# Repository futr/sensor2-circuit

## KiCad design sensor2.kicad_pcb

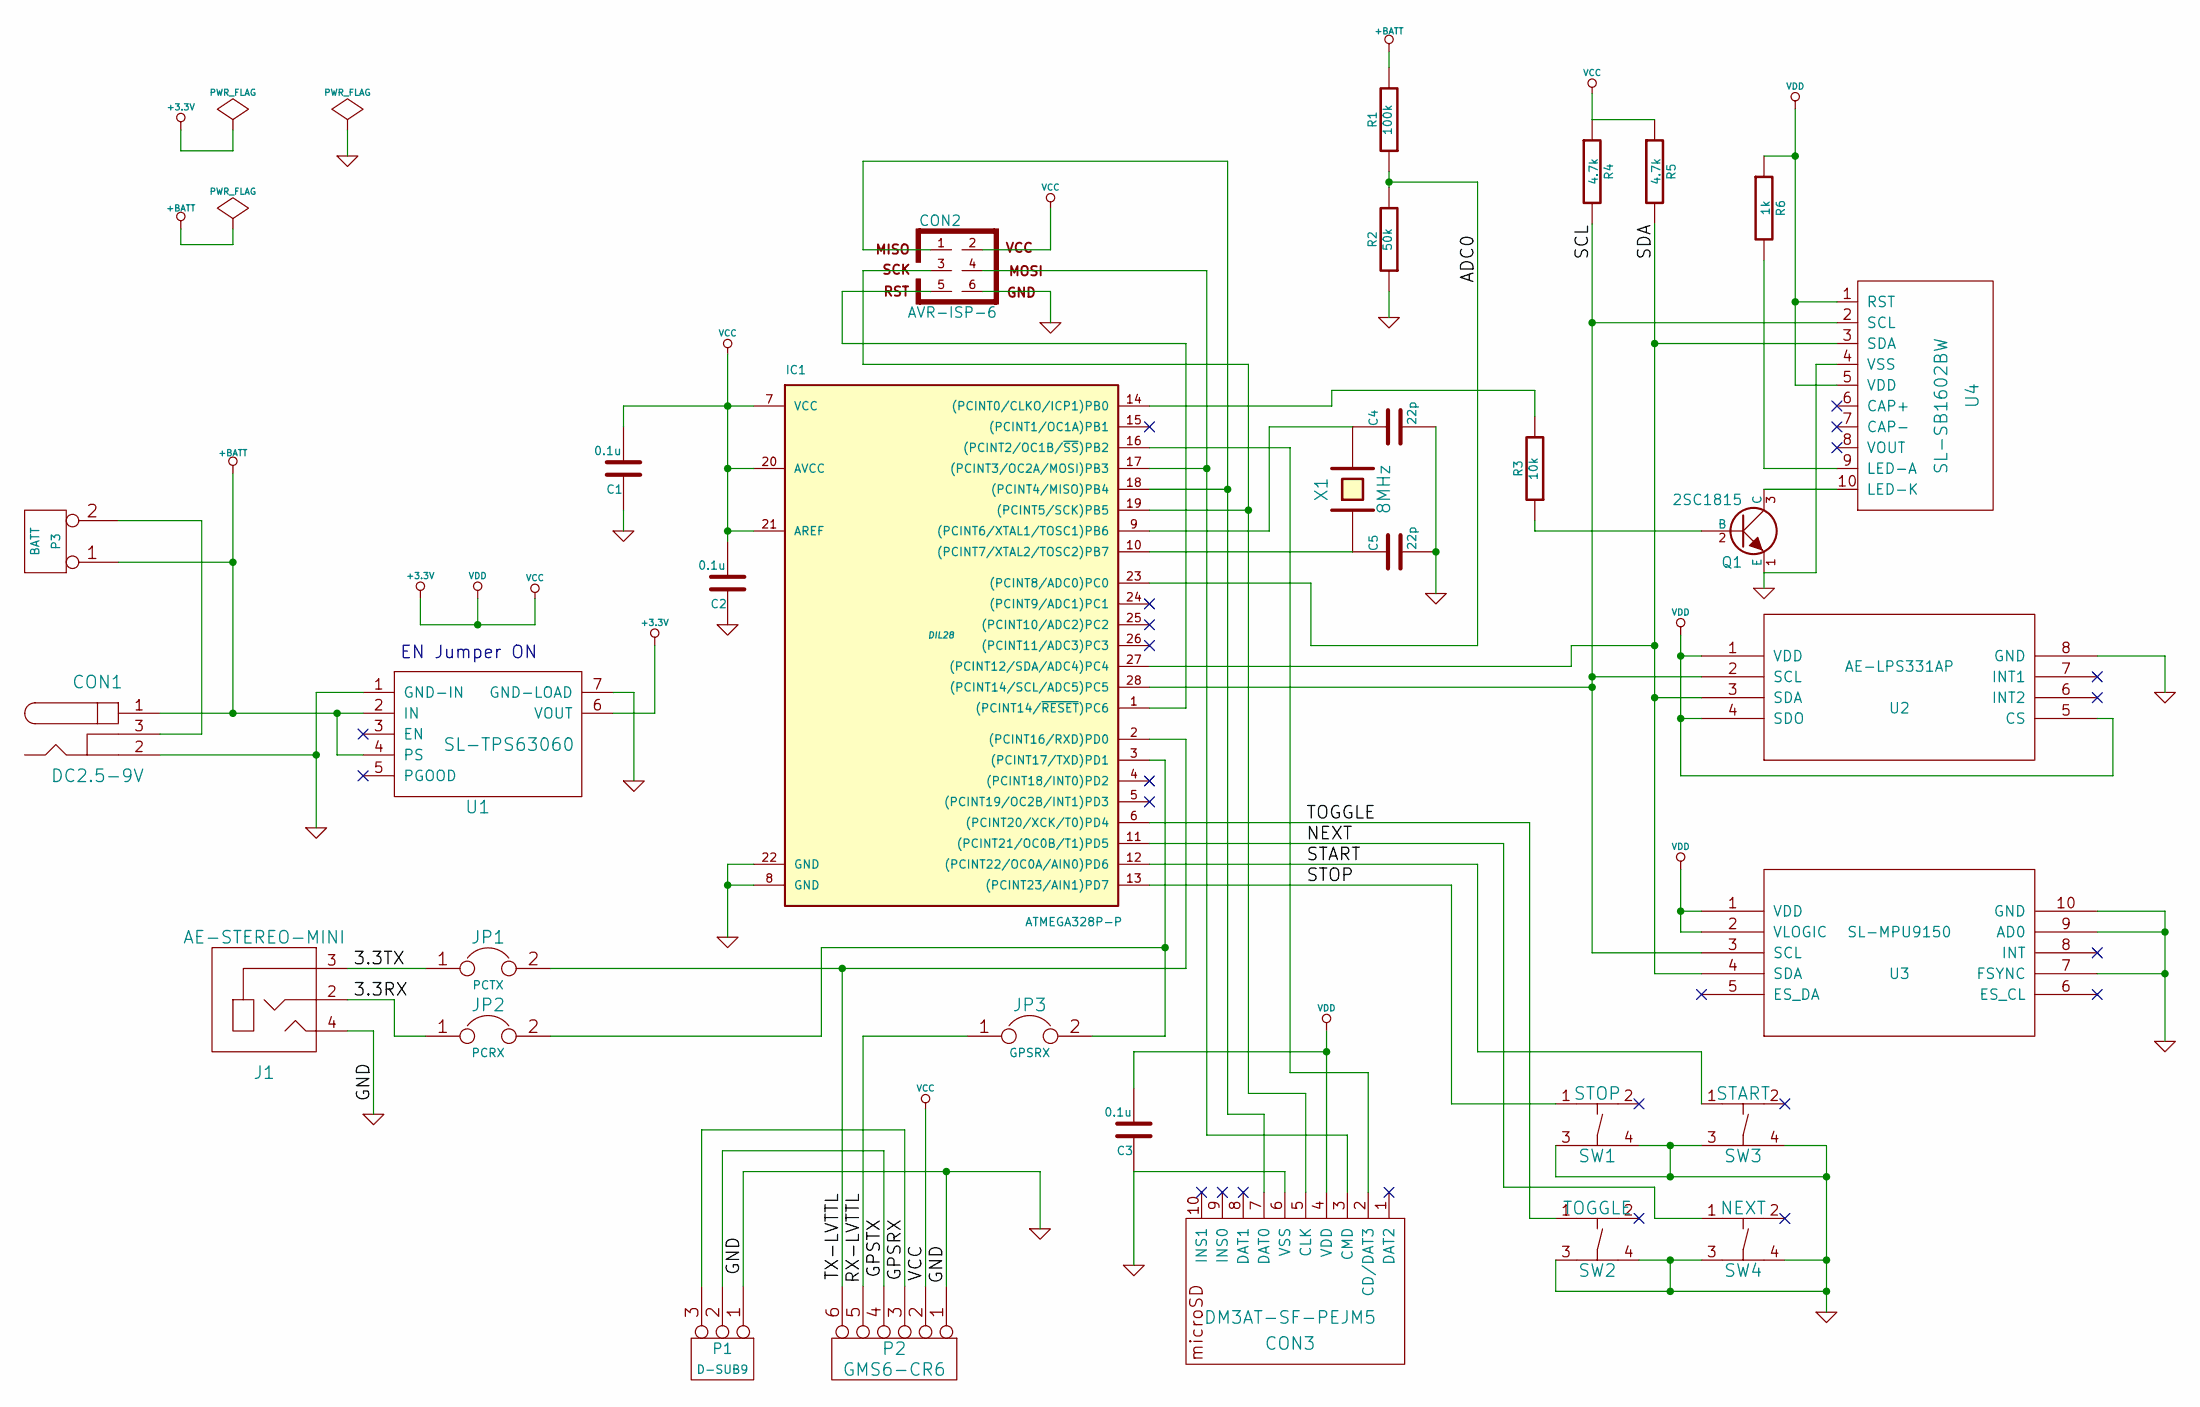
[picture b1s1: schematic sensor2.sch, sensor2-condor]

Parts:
C1, C2, C3: 0.1u
C4, C5: 22p
CON1: DC2.5-9V
CON2: AVR-ISP-6
CON3: DM3AT-SF-PEJM5
IC1: ATMEGA328P-P; DIL28
J1: AE-STEREO-MINI
JP1: PCTX
JP2: PCRX
JP3: GPSRX
P1: D-SUB9
P2: GMS6-CR6
P3: BATT
Q1: 2SC1815
R1: 100k
R2: 50k
R3: 10k
R4, R5: 4.7k
R6: 1k
SW1: STOP
SW2: TOGGLE
SW3: START
SW4: NEXT
U1: SL-TPS63060
U2: AE-LPS331AP; MODULE
U3: SL-MPU9150; MODULE
U4: SL-SB1602BW
X1: 8MHz

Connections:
+3.3V: C1.2, C2.2, C3.2, CON2.2, CON3.4 (VDD), IC1.7 (VCC), IC1.20 (AVCC), IC1.21 (AREF), P2.2, R4.1, R5.1, R6.1, U1.6 (VOUT), U2.1 (VDD), U2.4 (SDO), U2.5 (CS), U3.1 (VDD), U3.2 (VLOGIC), U4.1 (RST), U4.5 (VDD)
+BATT: CON1.1, P3.1, R1.2, U1.2 (IN), U1.4 (PS)
/3.3RX: J1.2, JP2.1
/3.3TX: J1.3, JP1.1
/ADC0: IC1.23 ((PCINT8/ADC0)PC0), R1.1, R2.2
/GPSRX: P1.3, P2.3
/GPSTX: P1.2 (PM), P2.4
/NEXT: IC1.11 ((PCINT21/OC0B/T1)PD5), SW4.1
/RX-LVTTL: JP3.1, P2.5
/SCL: IC1.28 ((PCINT14/SCL/ADC5)PC5), R4.2, U2.2 (SCL), U3.3 (SCL), U4.2 (SCL)
/SDA: IC1.27 ((PCINT12/SDA/ADC4)PC4), R5.2, U2.3 (SDA), U3.4 (SDA), U4.3 (SDA)
/START: IC1.12 ((PCINT22/OC0A/AIN0)PD6), SW3.1
/STOP: IC1.13 ((PCINT23/AIN1)PD7), SW1.1
/TOGGLE: IC1.6 ((PCINT20/XCK/T0)PD4), SW2.1
/TX-LVTTL: IC1.2 ((PCINT16/RXD)PD0), JP1.2, P2.6
GND: C1.1, C2.1, C3.1, C4.2, C5.2, CON1.2, CON2.6, CON3.6 (VSS), IC1.8 (GND), IC1.22 (GND), J1.4, P1.1, P2.1, Q1.1 (E), R2.1, SW1.3, SW1.4, SW2.3, SW2.4, SW3.3, SW3.4, SW4.3, SW4.4, U1.1 (GND-IN), U1.7 (GND-LOAD), U2.8 (GND), U3.7 (FSYNC), U3.9 (AD0), U3.10 (GND), U4.4 (VSS)
unnamed: CON2.4, CON3.3 (CMD), IC1.17 ((PCINT3/OC2A/MOSI)PB3)
unnamed: CON2.3, CON3.5 (CLK), IC1.19 ((PCINT5/SCK)PB5)
unnamed: IC1.14 ((PCINT0/CLKO/ICP1)PB0), R3.2
unnamed: Q1.2 (B), R3.1
unnamed: CON2.5, IC1.1 ((PCINT14/~RESET~)PC6)
unnamed: CON3.2 (CD/DAT3), IC1.16 ((PCINT2/OC1B/~SS~)PB2)
unnamed: Q1.3 (C), U4.10 (LED-K)
unnamed: CON2.1, CON3.7 (DAT0), IC1.18 ((PCINT4/MISO)PB4)
unnamed: R6.2, U4.9 (LED-A)
unnamed: CON1.3, P3.2 (PM)
unnamed: IC1.3 ((PCINT17/TXD)PD1), JP2.2, JP3.2
unnamed: C4.1, IC1.9 ((PCINT6/XTAL1/TOSC1)PB6), X1.2
unnamed: C5.1, IC1.10 ((PCINT7/XTAL2/TOSC2)PB7), X1.1

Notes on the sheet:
EN Jumper ON

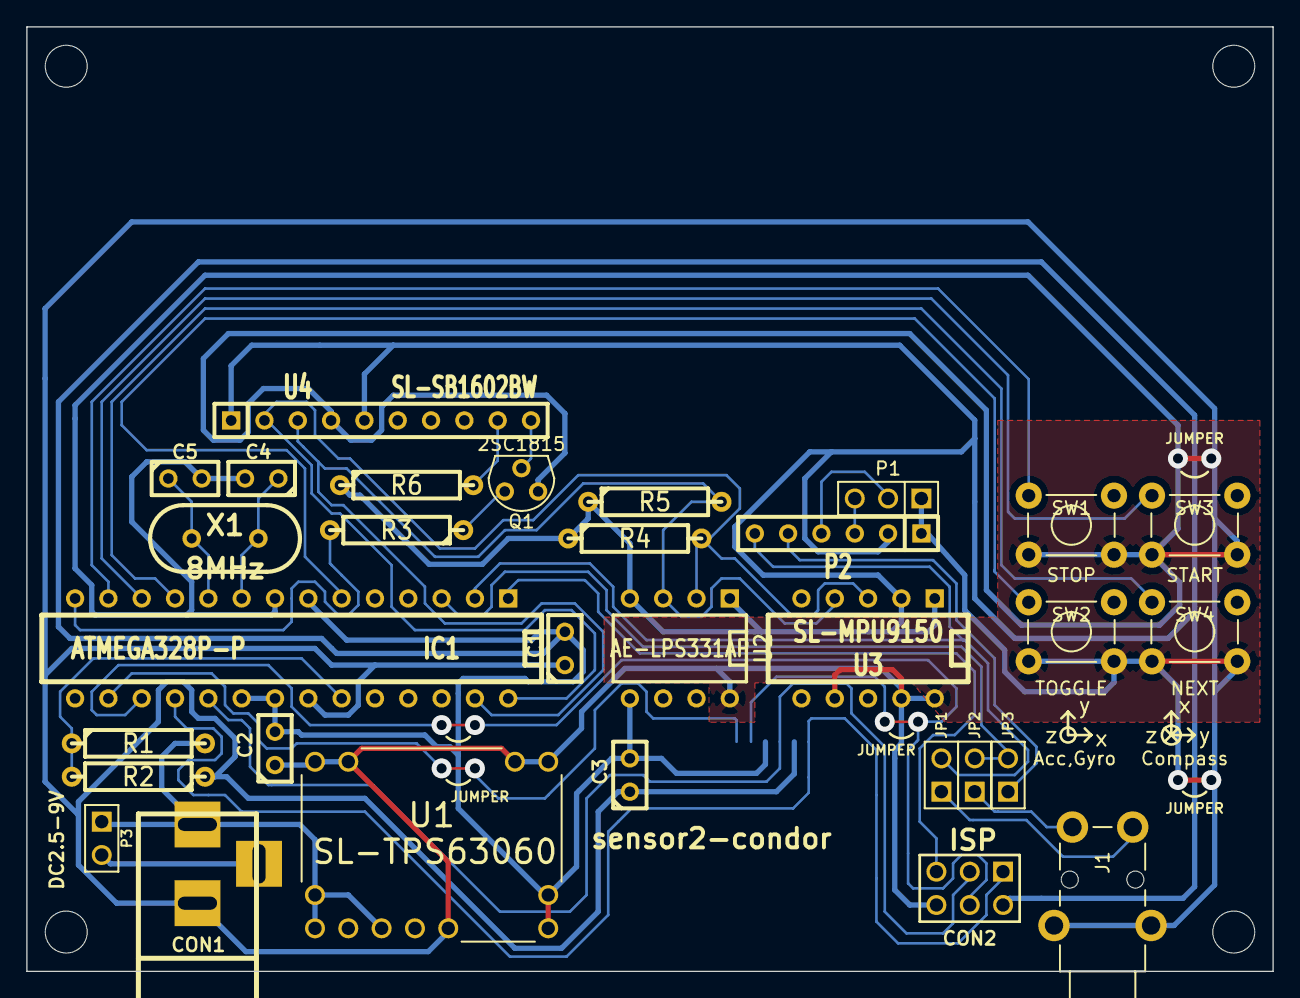
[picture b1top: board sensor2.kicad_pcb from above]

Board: 2 copper layers, 95.0 x 72.0 mm, 36 parts (1 on the bottom side), 29 nets.

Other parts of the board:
hole3-2mm, hole3-2mm#2, hole3-2mm#3, hole3-2mm#4: VAL**; hole3-2mm

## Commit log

2014-09-10 Developing
2014-09-11 Critical miss
2014-09-13 First release
2014-09-14 Rename spell miss
2014-09-14 Release
2015-01-22 Modify Q1
2015-01-22 Add circuit pdf
2015-02-11 Connect FSYNC pin to GND
